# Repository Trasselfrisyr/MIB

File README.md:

# MIB
MIDI Injector Box, merge controller data to MIDI

Makes use of the the FortySevenEffects Arduino MIDI Library, so make sure you've got that one.

For hardware, you can build the board from plans in the MIB-board folders to use together with a Pro Mini or use any MIDI shield together with an Arduino Uno.

Breath-Injector.ino - adds breath controller data to DIN-5 MIDI from a keyboard, great for creating a MIDI melodica. For use with breath controller synth patches responding to CC#2 (breath). Can easily be changed to send other CC data like volume or mod wheel by changing the CC_Number definition in the code.

Breath-Injector-ProMicroArcore.ino - version of breath injector above, using a Pro Micro and the Arcore arduino core for USB MIDI support. This version also transmits the breath data to USB. Made for the MIB mkII board.

Volume-Injector.ino - adds volume cc data. Build your own MIDI volume pedal perhaps?

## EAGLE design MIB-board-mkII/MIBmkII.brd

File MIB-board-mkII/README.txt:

General board for MIB projects. MIDI in (via optocoupler)
and out (via buffer), GVS pin groups for easy connection
of potentiometers, switches and LEDs to A0-A3 and digital
pins 10 through 13 on Pro Mini. Pins 10, 15, 14 and 15 on
Pro Micro. LED connectors with resistors on pins 5 and 6.
Board power is supplied via the USB port on the Pro Micro
and by supplying regulated 5V DC power to VCC/GND if using
Pro Mini. A micro USB board connected to the dedicated pins
on the GVS strip closest to the reset button, and a USB power
adapter is a good way to do this.

Component list:

1x Arduino Pro Mini or Pro Micro (socket recommended)
1x 6N138 or 6N139 optocoupler, DIP (socket recommended)
1x 74HC125 buffer, negative enable, DIP (socket recommended)
1x 1N4148 diode, mind the orientation
2x 2K2 resistor
5x 220 ohm resistor
1x 10K resistor
2x 100nF ceramic capacitor
2x PCB mount DIN-5 MIDI PCB connector
1x Tact Switch 6x6 mm
Breakable pin headers, black, red, white/yellow for GVS
Pin headers in black and green or blue for LED connectors,
and black headers for the Arduino, to plug it into the socket
(for a snug fit agains the socket, mount the header upside
down and cut the excess off the top after soldering.)

Notes:
The board uses the 74HC125 to disconnect the MIDI circuits for
problem free reprogramming of the Pro Mini. To enable the MIDI
connection, you must set pin 2 low in the Arduino sketch.

pinMode(2,OUTPUT);
digitalWrite(2,LOW); // set pin 2 low to enable DIN MIDI

This is if you write your own code. In the MIB code projects
available on github, this is already done.

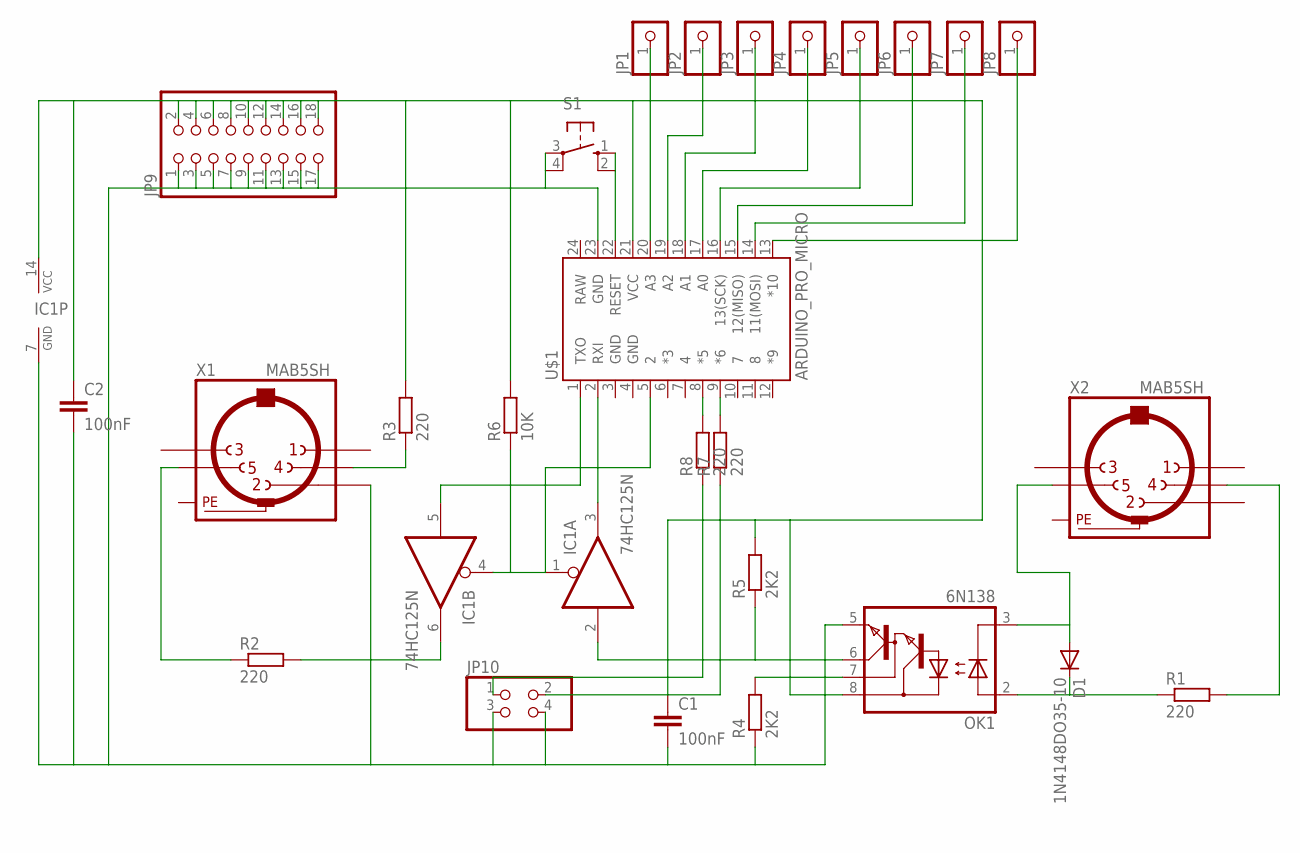
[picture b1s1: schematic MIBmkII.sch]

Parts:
C1, C2: 100nF; C075-032X103
D1: 1N4148DO35-10; DO35-10
IC1: 74HC125N; DIL14
JP1, JP2, JP3, JP4, JP5, JP6, JP7, JP8: PINHD-1X1; 1X01
JP9: PINHD-2X9; 2X09
JP10: PINHD-2X2; 2X02
OK1: 6N138; DIL08
R1, R2, R3, R7, R8: 220; 0207/10
R4, R5: 2K2; 0207/10
R6: 10K; 0207/10
S1: 10-XX; B3F-10XX
U$1: ARDUINO_PRO_MICRO
X1, X2: MAB5SH

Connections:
unnamed: IC1.3 (O), U$1.2 (RXI)
unnamed: IC1.5 (I), U$1.1 (TXO)
unnamed: IC1.1 (OE), IC1.4 (OE), R6.1, U$1.5 (2)
unnamed: C1.1, C2.1, IC1.14 (VCC), JP9.2, JP9.4, JP9.6, JP9.8, JP9.10, JP9.12, JP9.14, JP9.16, JP9.18, OK1.8 (VCC), R3.2, R5.2, R6.2, U$1.21 (VCC)
unnamed: C1.2, C2.2, IC1.7 (GND), JP9.1, JP9.3, JP9.5, JP9.7, JP9.9, JP9.11, JP9.13, JP9.15, JP9.17, JP10.3, JP10.4, OK1.5 (GND), R4.1, S1.3, S1.4 (P1), U$1.23 (GND), X1.2
unnamed: D1.C, OK1.2 (A), R1.1
unnamed: D1.A, OK1.3 (C), X2.5
unnamed: OK1.7 (VB), R4.2
unnamed: IC1.2 (I), OK1.6 (VO), R5.1
unnamed: R3.1, X1.4
unnamed: IC1.6 (O), R2.2
unnamed: R2.1, X1.5
unnamed: R1.2, X2.4
unnamed: JP1.1, U$1.20 (A3)
unnamed: JP2.1, U$1.19 (A2)
unnamed: JP3.1, U$1.18 (A1)
unnamed: JP4.1, U$1.17 (A0)
unnamed: JP5.1, U$1.16 (13(SCK))
unnamed: JP6.1, U$1.15 (12(MISO))
unnamed: JP7.1, U$1.14 (11(MOSI))
unnamed: JP8.1, U$1.13 (*10)
unnamed: R7.2, U$1.9 (*6)
unnamed: R8.2, U$1.8 (*5)
unnamed: JP10.1, R8.1
unnamed: JP10.2, R7.1
unnamed: S1.1 (S), S1.2 (S1), U$1.22 (RESET)
PE: X1.PE, X1.PE@ (PE), X2.PE, X2.PE@ (PE)

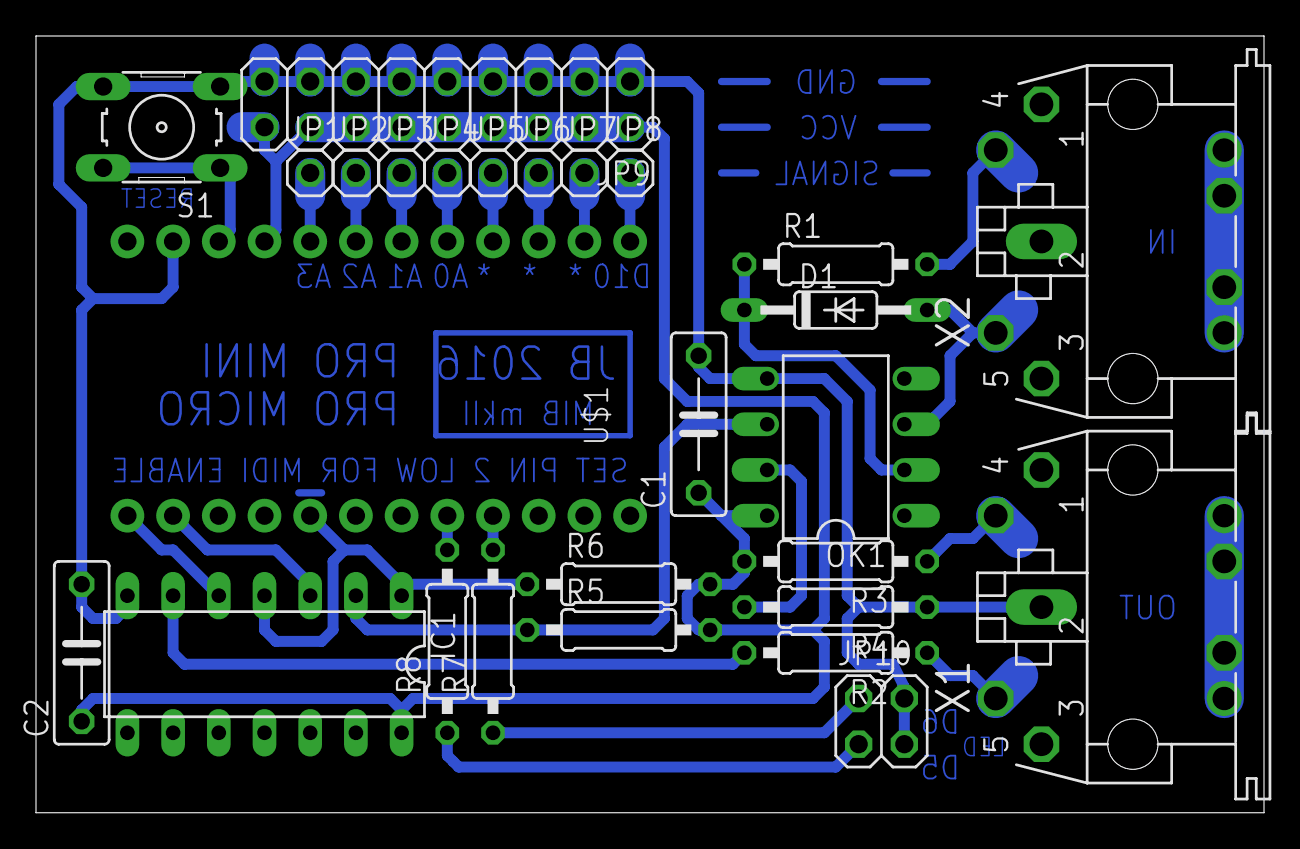
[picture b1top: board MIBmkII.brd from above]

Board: 2 copper layers, 68.2 x 43.2 mm, 27 parts (0 on the bottom side), 27 nets.

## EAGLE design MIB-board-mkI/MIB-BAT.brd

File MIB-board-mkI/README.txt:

General board for MIB projects. MIDI in (via optocoupler)
and out (via optional buffer), GVS pin groups for easy connection
of potentiometers, switches and LEDs to A0-A3 and digital pins
10, 11 and 12. Optional battery power supply part with soldered
in charge/step-up board.

Component list:

1x Arduino Pro Mini
1x 6N137, 6N138 or 6N139 optocoupler, DIP (OK2)
1x 74LS14 buffer/inverter, DIP, optional (IC1)
1x 1N4148 diode, mind the orientation (D1)
2x 2K2 resistor (if 6N137, just one) (R3, R5*)
3x 220 ohm resistor (R1, R2, R4)
2x PCB mount DIN-5 MIDI PCB connector (X1, X2)
1x Slide switch DPDT (2.54 mm pin separation) (S1)
Breakable pin headers, black, red, white for GVS

Optional power circuit:

Battery holder 16340
Li-Ion battery 3.7V 16340
All-in-one charge and step-up board (r.ebay.com/uWUNOm)

VOUT +/- connects to PWR +/- of main circuit via a switch.
VIN +/- connects to panel mount power jack for 5V input.

Notes for assembling:

If the 74LS14 DIP is installed, the jumper pads marked <<>> are
left unconnected. If DIP is not installed, bridge the pads with
a jumper to connect the TX line to the output.

If the optocoupler selected for the build is a 6N137, the 2K2
resistor where PCB is marked >137 (R5) is omitted.

The slide switch on the board is for disconnecting the TX and RX
lines when uploading new programs to the Arduino. If you can't find
a DPDT switch that fits, you could go with single slide switches or
probably DIP switches too. Or jumpers.

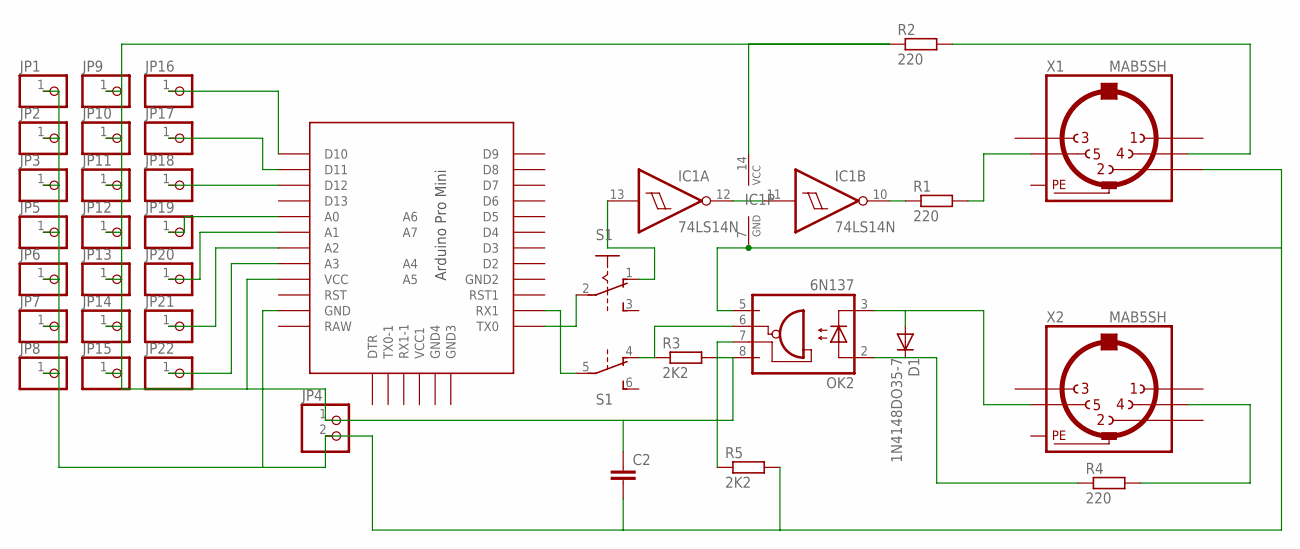
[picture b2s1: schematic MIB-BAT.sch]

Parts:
C2: C7.5/3; C7.5B3
D1: 1N4148DO35-7; DO35-7
IC1: 74LS14N; DIL14
JP1, JP2, JP3, JP5, JP6, JP7, JP8, JP9, JP10, JP11, JP12, JP13, JP14, JP15, JP16, JP17, JP18, JP19, JP20, JP21, JP22: PINHD-1X1; 1X01
JP4: PINHD-1X2; 1X02
OK2: 6N137; DIL08
R1, R2, R4: 220; 0207/10
R3, R5: 2K2; 0207/10
S1: A68-A31
U$1: PRO-MINI-2
X1, X2: MAB5SH

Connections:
unnamed: S1.5, U$1.RX1
unnamed: IC1.11 (I), IC1.12 (O)
unnamed: IC1.10 (O), R1.1
unnamed: D1.C, OK2.2 (A), R4.1
unnamed: R4.2, X2.4
unnamed: D1.A, OK2.3 (C), X2.5
unnamed: R1.2, X1.5
unnamed: R2.2, X1.4
unnamed: OK2.6 (VO), R3.1, S1.4 (O)
unnamed: C2.2, IC1.7 (GND), JP1.1, JP2.1, JP3.1, JP4.2, JP5.1, JP6.1, JP7.1, JP8.1, OK2.5 (GND), R5.2, U$1.GND, X1.2
unnamed: JP16.1, U$1.D10
unnamed: JP17.1, U$1.D11
unnamed: C2.1, IC1.14 (VCC), JP4.1, JP9.1, JP10.1, JP11.1, JP12.1, JP13.1, JP14.1, JP15.1, OK2.8 (VCC), R2.1, R3.2, U$1.VCC
unnamed: JP18.1, U$1.D12
unnamed: JP19.1, U$1.A0
unnamed: JP20.1, U$1.A1
unnamed: S1.2, U$1.TX0
unnamed: JP21.1, U$1.A2
unnamed: JP22.1, U$1.A3
unnamed: OK2.7 (VE), R5.1
unnamed: IC1.13 (I), S1.1 (O)
PE: X1.PE, X1.PE@ (PE), X2.PE, X2.PE@ (PE)

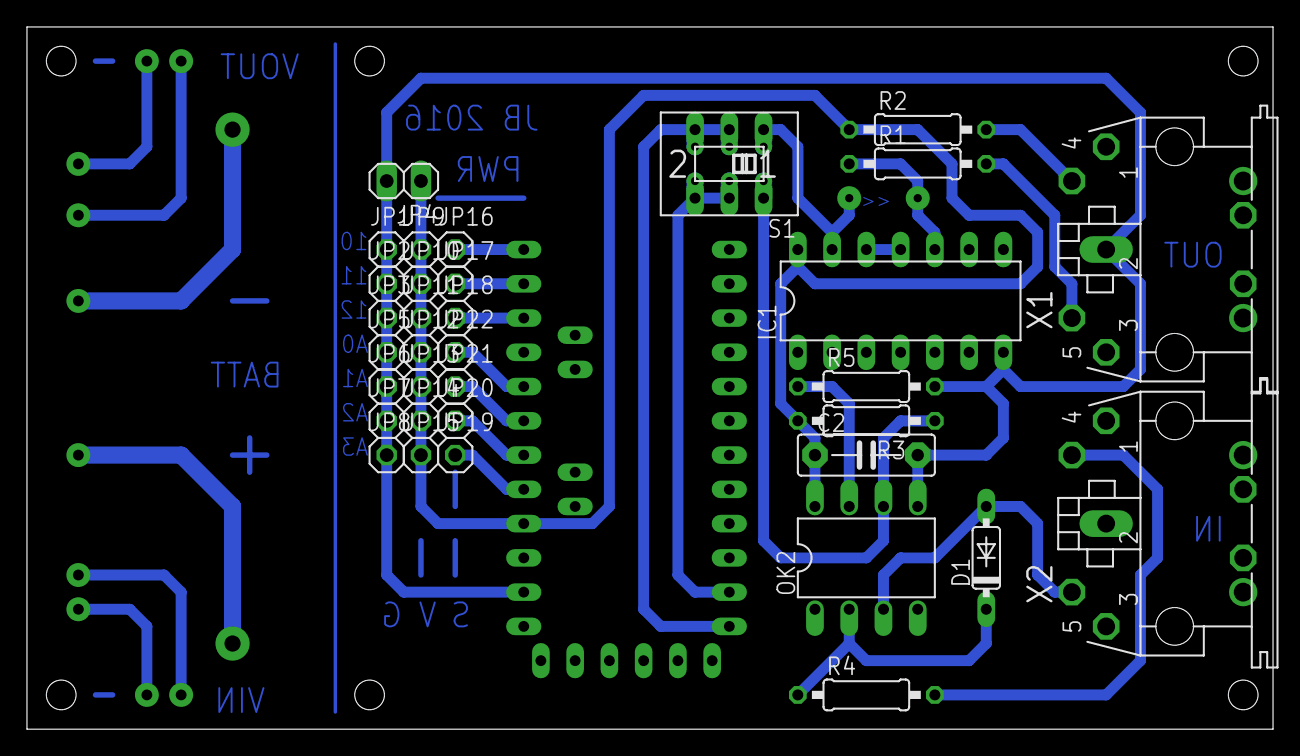
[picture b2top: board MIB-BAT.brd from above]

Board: 2 copper layers, 92.4 x 52.1 mm, 35 parts (0 on the bottom side), 22 nets.

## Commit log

2016-07-13 Added untested code and schematic.
2016-07-13 Cleanup and making sure CC value 0 is sent when off threshold. Removed DIP switches for channel selection. New schematic.
2016-07-13 Updated readme with info on Breath Injector
2016-07-13 Cleanup.
2016-07-14 Made it easier to change the CC number.
2016-08-03 Changed sensor to MPXV5004GP and modified values accordingly.
2016-08-05 Upped the on threshold a bit.
2016-08-06 Updated schematic image
2016-08-22 Added optional potentiometers for easy adjustment. Added smoothing and sending of channel aftertouch data.
2016-08-31 Added schematics and PCB transfer files for making a MIDI circuit board for the MIB projects. Runs on regulated 5V input.
2016-08-31 Weblink to recommended power board.
2016-09-01 Better version board with optional battery power supply
2016-09-01 no message
2016-09-01 Info in readme file.
2016-09-01 Added info to readme file.
2016-09-02 New PCB layout enabling choice of optocoupler and makes the buffer optional.
2016-09-02 Transfer and readme small fixes.
2016-09-03 Added sketch for Volume Injector.
2016-10-02 New mkII board design added. Breath injector code for Pro Micro and Arcore added.
2016-10-02 Added pictures and schematics.
2016-10-08 Updated code with pin 2 MIDI enable for MIB mkII board
2016-10-08 Better silkscreen, smaller pdf area for easier multiple prints per page
2016-10-08 Added readme file.
2016-10-09 Corrected labeling on silkscreen. Increased size of some pads and traces.

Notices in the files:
parts and their libraries:
SparkFun-Boards: Licensing: Creative Commons ShareAlike 4.0 International - https://creativecommons.org/licenses/by-sa/4.0
